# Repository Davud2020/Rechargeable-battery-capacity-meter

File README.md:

# Rechargeable-battery-capacity-meter
### Link
https://danyk.cz/avr_aku_en.html

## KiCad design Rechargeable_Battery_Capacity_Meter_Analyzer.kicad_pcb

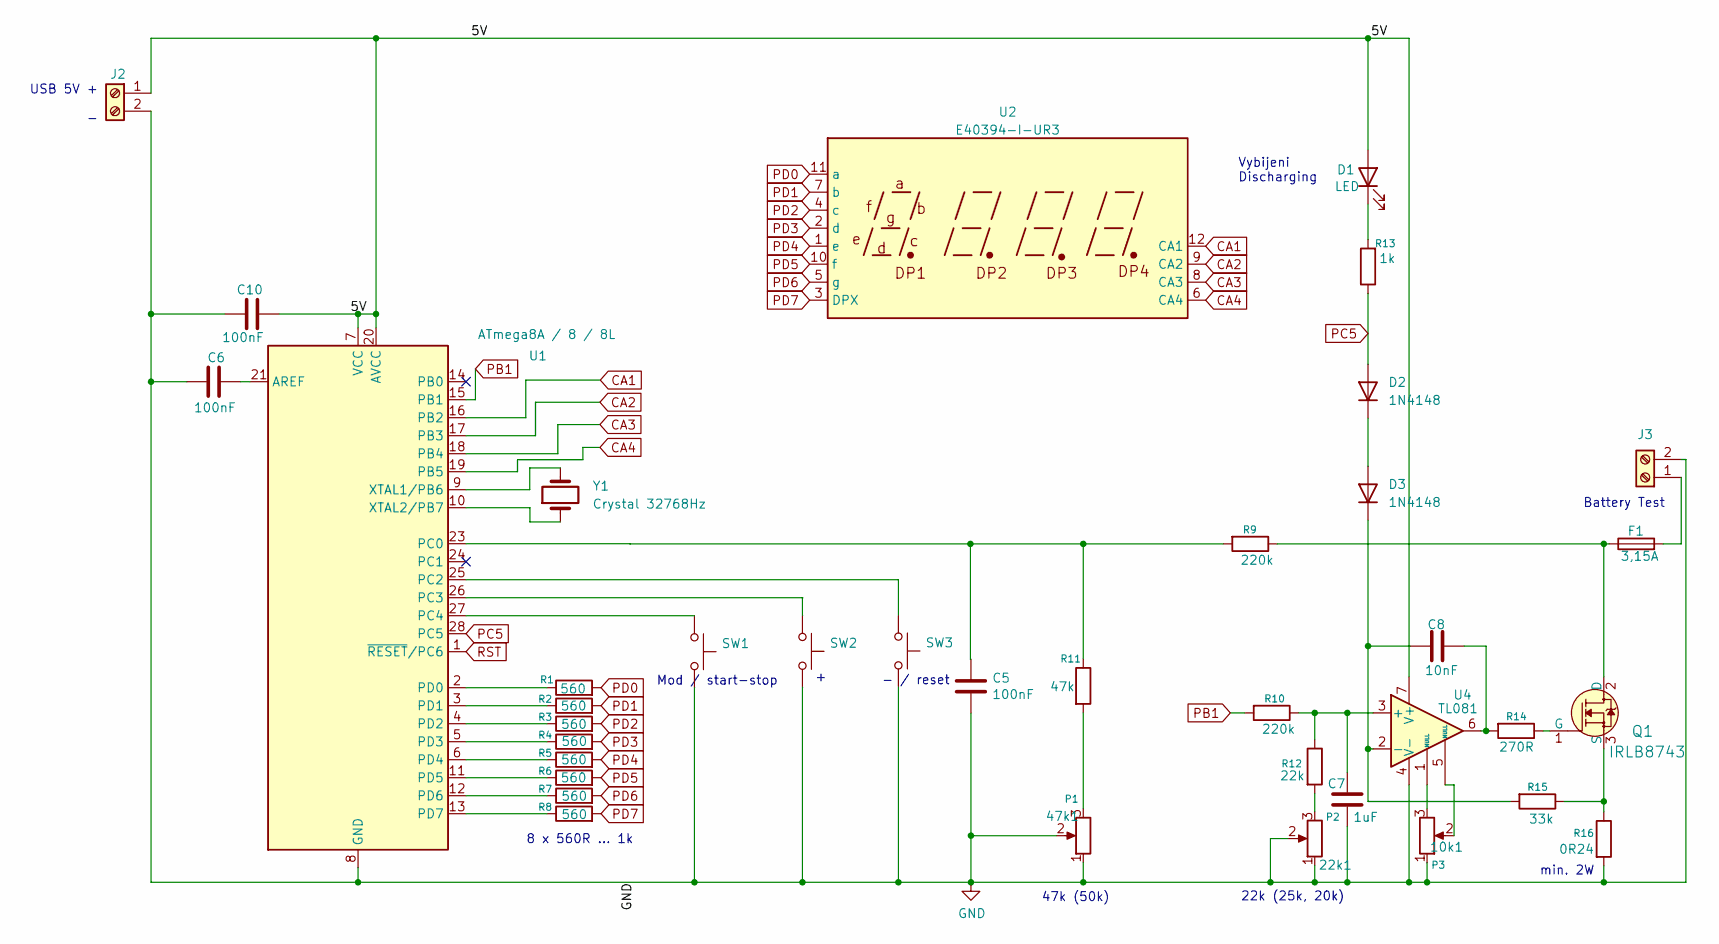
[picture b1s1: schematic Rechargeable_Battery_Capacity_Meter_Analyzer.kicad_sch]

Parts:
10k1: P3; Potentiometer_ACP_CA9-V10_Vertical_Hole
22k1: P2; Potentiometer_ACP_CA9-V10_Vertical_Hole
47k1: P1; Potentiometer_ACP_CA9-V10_Vertical_Hole
C5, C6, C10: 100nF; C_Disc_D4.7mm_W2.5mm_P5.00mm
C7: 1uF; C_Disc_D4.7mm_W2.5mm_P5.00mm
C8: 10nF; C_Disc_D4.7mm_W2.5mm_P5.00mm
D1: LED; LED_D3.0mm
D2, D3: 1N4148; D_DO-35_SOD27_P7.62mm_Horizontal
F1: 3,15A; Fuse_Littelfuse_372_D8.50mm
J2: Power; TerminalBlock_4Ucon_1x02_P3.50mm_Horizontal
J3: Test; TerminalBlock_4Ucon_1x02_P3.50mm_Horizontal
Q1: IRLB8743; TO-220-3; MPN IRLB8721PBF; Digi-Key_PN IRLB8721PBF-ND
R1, R2, R3, R4, R5, R6, R7, R8: 560; R_Axial_DIN0204_L3.6mm_D1.6mm_P7.62mm_Horizontal
R9, R10: 220k; R_Axial_DIN0204_L3.6mm_D1.6mm_P7.62mm_Horizontal
R11: 47k; R_Axial_DIN0204_L3.6mm_D1.6mm_P7.62mm_Horizontal
R12: 22k; R_Axial_DIN0204_L3.6mm_D1.6mm_P7.62mm_Horizontal
R13: 1k; R_Axial_DIN0204_L3.6mm_D1.6mm_P7.62mm_Horizontal
R14: 270R; R_Axial_DIN0204_L3.6mm_D1.6mm_P7.62mm_Horizontal
R15: 33k; R_Axial_DIN0204_L3.6mm_D1.6mm_P7.62mm_Horizontal
R16: 0R24; R_Axial_Power_L20.0mm_W6.4mm_P25.40mm
SW1, SW2, SW3: SW_Tactile_Straight_KSA0Axx1LFTR
U1: ATmega8A / 8 / 8L; DIP-28_W7.62mm
U2: E40394-I-UR3; E40394-l-UR3
U4: TL081; DIP-8_W7.62mm_LongPads
Y1: Crystal 32768Hz; Crystal_HC18-U_Vertical

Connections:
/5V: C10.2, D1.2 (A), J2.1, U1.7 (VCC), U1.20 (AVCC), U4.7 (V+)
CA1: U1.16 (PB2), U2.12 (CA1)
CA2: U1.17 (PB3), U2.9 (CA2)
CA3: U1.18 (PB4), U2.8 (CA3)
CA4: U1.19 (PB5), U2.6 (CA4)
GND: 10k1.1, 22k1.1, 22k1.2, 47k1.1, 47k1.2, C5.2, C6.1, C7.2, C10.1, J2.2, J3.2, R16.2, SW1.2, SW2.2, SW3.2, U1.8 (GND), U1.22 (GND), U4.4 (V-)
unnamed: 10k1.2, U4.5 (NULL)
unnamed: 10k1.3, U4.1 (NULL)
unnamed: 22k1.3, R12.2
unnamed: 47k1.3, R11.2
unnamed: C8.2, R14.2, U4.6
unnamed: D1.1 (K), R13.2
unnamed: D2.1 (K), D3.2 (A)
unnamed: C8.1, D3.1 (K), R15.2, U4.2 (-)
unnamed: F1.2, J3.1
unnamed: F1.1, Q1.2 (D), R9.1
unnamed: Q1.1 (G), R14.1
unnamed: Q1.3 (S), R15.1, R16.1
unnamed: C6.2, U1.21 (AREF)
unnamed: C5.1, R9.2, R11.1, U1.23 (PC0)
unnamed: SW3.1, U1.25 (PC2)
unnamed: SW2.1, U1.26 (PC3)
unnamed: SW1.1, U1.27 (PC4)
unnamed: R1.1, U1.2 (PD0)
unnamed: R2.1, U1.3 (PD1)
unnamed: R3.1, U1.4 (PD2)
unnamed: R4.1, U1.5 (PD3)
unnamed: R5.1, U1.6 (PD4)
unnamed: R6.1, U1.11 (PD5)
unnamed: R7.1, U1.12 (PD6)
unnamed: R8.1, U1.13 (PD7)
unnamed: U1.9 (XTAL1/PB6), Y1.2
unnamed: U1.10 (XTAL2/PB7), Y1.1
unnamed: C7.1, R10.1, R12.1, U4.3 (+)
PB1: R10.2, U1.15 (PB1)
PC5: D2.2 (A), R13.1, U1.28 (PC5)
PD0: R1.2, U2.11 (a)
PD1: R2.2, U2.7 (b)
PD2: R3.2, U2.4 (c)
PD3: R4.2, U2.2 (d)
PD4: R5.2, U2.1 (e)
PD5: R6.2, U2.10 (f)
PD6: R7.2, U2.5 (g)
PD7: R8.2, U2.3 (DPX)
RST: U1.1 (~RESET/PC6)

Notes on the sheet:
Mod / start-stop
min. 2W
Battery Test
USB 5V + -
22k (25k, 20k)
Vybijeni Discharging
8 x 560R ... 1k
- / reset
47k (50k)

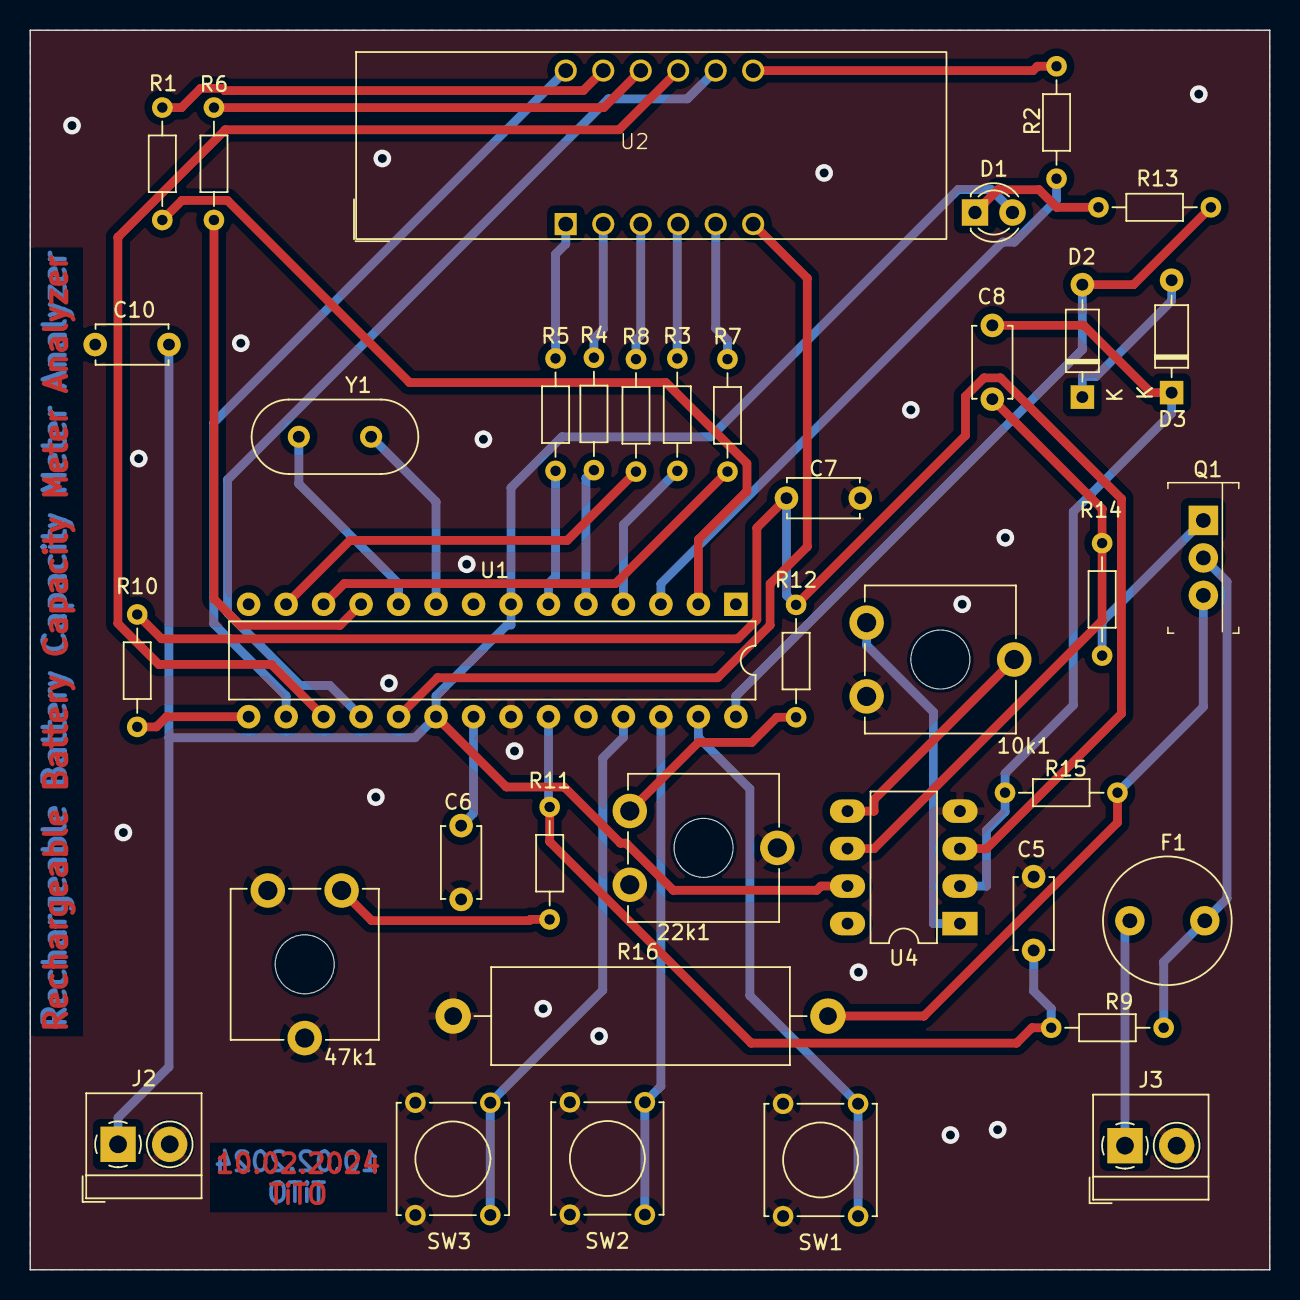
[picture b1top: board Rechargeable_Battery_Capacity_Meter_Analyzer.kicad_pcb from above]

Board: 2 copper layers, 84.0 x 84.0 mm, 38 parts (0 on the bottom side), 44 nets.
